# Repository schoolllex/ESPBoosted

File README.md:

# Custom ESP32-WROOM-32 All-in-One DevBoard

A custom, feature-rich ESP32-WROOM-32 development board featuring built-in environmental sensors, power management, and expansion interfaces. All project files, schematics, and manufacturing assets are included in the `.zip` archive within this repository.

## Features

* **Core & Programming:** ESP32-WROOM-32E module with onboard CH340K USB-to-UART bridge and automatic flash circuit.
* **Power Management:** AP2112K-3.3 LDO regulator, TP4056 LiPo battery charger, and power path management.
* **Sensors & Peripherals:**
* BME280 (Temperature, Humidity, Pressure)
* TSL25911FN (Digital Light Sensor)
* MPU-6050 (6-axis IMU / Accelerometer & Gyroscope)
* WS2812B RGB NeoPixel LED & Passive Piezo Buzzer
* MicroSD Card Slot (SPI mode)

* **Expansion:** MCP23017 16-bit I/O expander, ADS1115 16-bit ADC, and a Qwiic/STEMMA QT connector.

## Getting Started

1. Download and extract the project files from the `.zip` archive in this repository.
2. Open the project in **KiCad** to view schematics, layouts, and manufacturing files (Gerber/BOM/CPL).
3. Connect the board to your computer via a USB-C cable.
4. Flash your code using the Arduino IDE or your preferred development environment.
5. Enjoy your custom DevBoard!

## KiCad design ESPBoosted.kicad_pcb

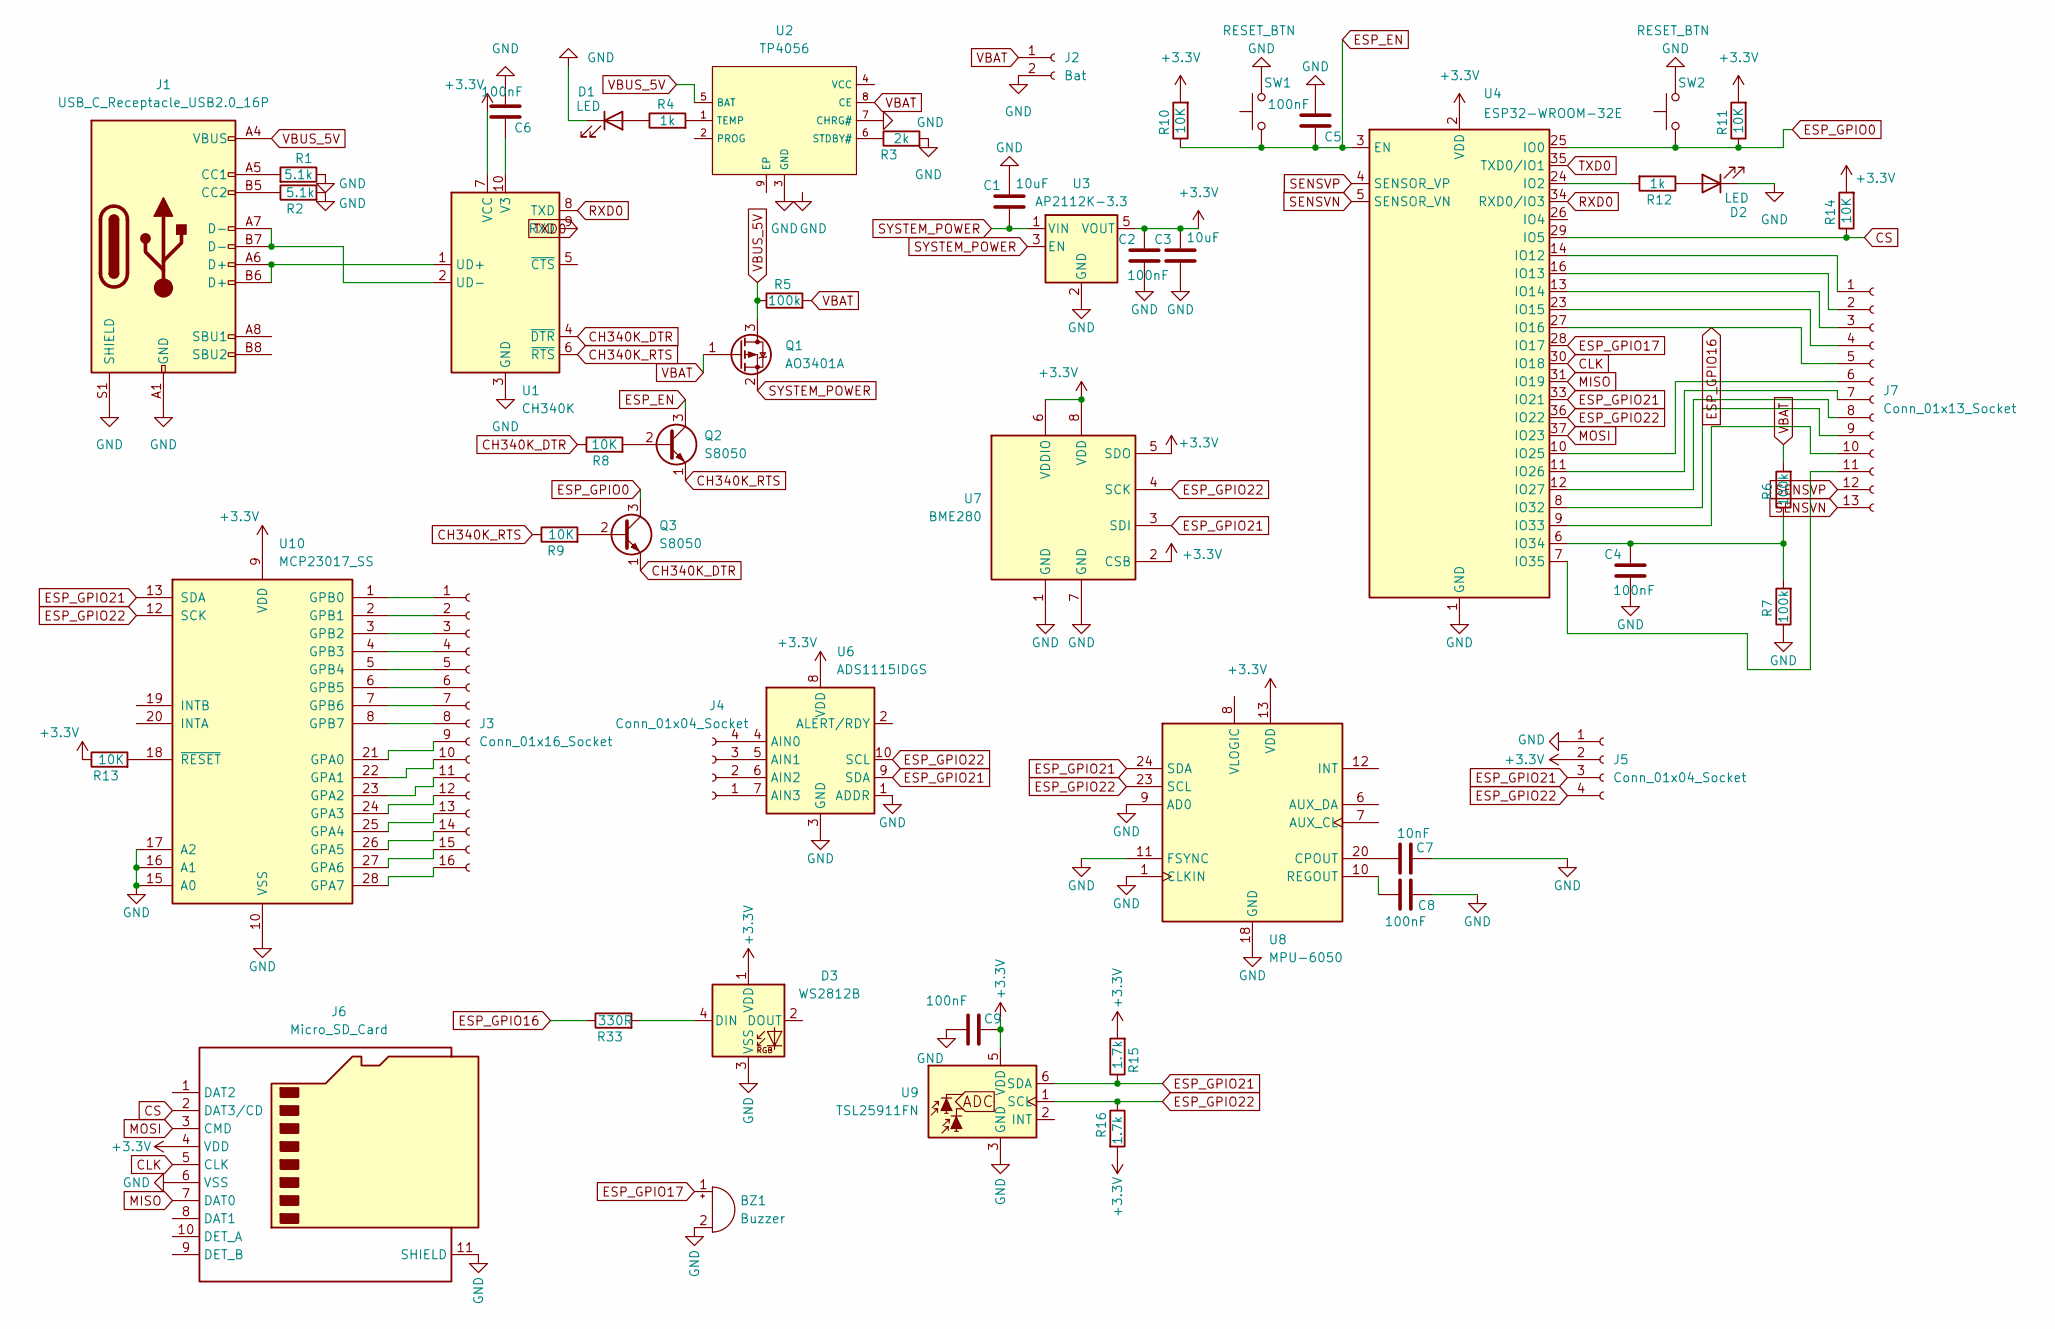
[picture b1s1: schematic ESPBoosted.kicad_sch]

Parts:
BZ1: Buzzer; Buzzer_CUI_CPT-9019S-SMT
C1, C3: 10uF; C_0805_2012Metric
C2, C4, C5, C6, C8, C9: 100nF; C_0805_2012Metric
C7: 10nF; C_0805_2012Metric
D1, D2: LED; LED_WS2812B_PLCC4_5.0x5.0mm_P3.2mm
D3: WS2812B; LED_WS2812B_PLCC4_5.0x5.0mm_P3.2mm
J1: USB_C_Receptacle_USB2.0_16P; USB_C_Receptacle_HRO_TYPE-C-31-M-12
J2: Bat; TerminalBlock_bornier-2_P5.08mm
J3: Conn_01x16_Socket; PinHeader_1x16_P1.00mm_Horizontal
J4, J5: Conn_01x04_Socket; PinHeader_1x04_P1.00mm_Horizontal
J6: Micro_SD_Card; microSD_HC_Hirose_DM3AT-SF-PEJM5
J7: Conn_01x13_Socket; PinHeader_1x13_P1.00mm_Horizontal
Q1: AO3401A; SOT-23
Q2, Q3: S8050; TO-92_Inline
R1, R2: 5.1k; R_0805_2012Metric
R3: 2k; R_0805_2012Metric
R4, R12: 1k; R_0805_2012Metric
R5, R6, R7: 100k; R_0805_2012Metric
R8, R9, R10, R11, R13, R14: 10K; R_0805_2012Metric
R15, R16: 1.7k; R_0805_2012Metric
R33: 330R; R_0805_2012Metric
SW1, SW2: RESET_BTN; SW_SPST_PTS645
U1: CH340K; SSOP-10-1EP_3.9x4.9mm_P1mm_EP2.1x3.3mm
U2: TP4056; HSOP-8-1EP_3.9x4.9mm_P1.27mm_EP2.3x2.3mm_ThermalVias; Part TP4056-42-ESOP8; LCSC C16581
U3: AP2112K-3.3; SOT-23-5
U4: ESP32-WROOM-32E; ESP32-WROOM-32
U6: ADS1115IDGS; MSOP-10_3x3mm_P0.5mm
U7: BME280; Bosch_LGA-8_2.5x2.5mm_P0.65mm_ClockwisePinNumbering
U8: MPU-6050; InvenSense_QFN-24_4x4mm_P0.5mm
U9: TSL25911FN; Broadcom_DFN-6_2x2mm_P0.65mm
U10: MCP23017_SS; SSOP-28_5.3x10.2mm_P0.65mm

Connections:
+3.3V: C2.1, C3.1, C9.2, D3.1 (VDD), J5.2, J6.4 (VDD), R10.2, R11.2, R13.1, R14.2, R15.2, R16.2, U1.7 (VCC), U3.5 (VOUT), U4.2 (VDD), U6.8 (VDD), U7.2 (CSB), U7.5 (SDO), U7.6 (VDDIO), U7.8 (VDD), U8.13 (VDD), U9.5 (VDD), U10.9 (VDD)
CH340K_DTR: Q3.1 (E), R8.1, U1.4 (~DTR)
CH340K_RTS: Q2.1 (E), R9.1, U1.6 (~RTS)
CLK: J6.5 (CLK), U4.30 (IO18)
CS: J6.2 (DAT3/CD), R14.1, U4.29 (IO5)
ESP_EN: C5.1, Q2.3 (C), R10.1, SW1.1, U4.3 (EN)
ESP_GPIO0: Q3.3 (C), R11.1, SW2.1, U4.25 (IO0)
ESP_GPIO16: J7.5, R33.1, U4.27 (IO16)
ESP_GPIO17: BZ1.1 (+), U4.28 (IO17)
ESP_GPIO21: J5.3, R15.1, U4.33 (IO21), U6.9 (SDA), U7.3 (SDI), U8.24 (SDA), U9.6 (SDA), U10.13 (SDA)
ESP_GPIO22: J5.4, R16.1, U4.36 (IO22), U6.10 (SCL), U7.4 (SCK), U8.23 (SCL), U9.1 (SCL), U10.12 (SCK)
GND: BZ1.2 (-), C1.1, C2.2, C3.2, C4.2, C5.2, C6.2, C7.2, C8.2, C9.1, D1.1 (K), D2.1 (K), D3.3 (VSS), J1.A1 (GND), J1.A12 (GND), J1.B1 (GND), J1.B12 (GND), J1.S1 (SHIELD), J2.2, J5.1, J6.6 (VSS), J6.11 (SHIELD), R1.1, R2.2, R3.2, R7.1, SW1.2, SW2.2, U1.3 (GND), U1.11 (GND), U2.3 (GND), U2.7 (CHRG#), U3.2 (GND), U4.1 (GND), U4.15 (GND), U4.38 (GND), U4.39 (GND), U6.1 (ADDR), U6.3 (GND), U7.1 (GND), U7.7 (GND), U8.1 (CLKIN), U8.9 (AD0), U8.11 (FSYNC), U8.18 (GND), U9.3 (GND), U10.10 (VSS), U10.15 (A0), U10.16 (A1), U10.17 (A2)
MISO: J6.7 (DAT0), U4.31 (IO19)
MOSI: J6.3 (CMD), U4.37 (IO23)
unnamed: D1.2 (A), R4.1
unnamed: D2.2 (A), R12.1
unnamed: D3.4 (DIN), R33.2
unnamed: J1.A5 (CC1), R1.2
unnamed: J1.B5 (CC2), R2.1
unnamed: J3.1, U10.1 (GPB0)
unnamed: J3.2, U10.2 (GPB1)
unnamed: J3.3, U10.3 (GPB2)
unnamed: J3.4, U10.4 (GPB3)
unnamed: J3.5, U10.5 (GPB4)
unnamed: J3.6, U10.6 (GPB5)
unnamed: J3.7, U10.7 (GPB6)
unnamed: J3.8, U10.8 (GPB7)
unnamed: J3.9, U10.21 (GPA0)
unnamed: J3.10, U10.22 (GPA1)
unnamed: J3.11, U10.23 (GPA2)
unnamed: J3.12, U10.24 (GPA3)
unnamed: J3.13, U10.25 (GPA4)
unnamed: J3.14, U10.26 (GPA5)
unnamed: J3.15, U10.27 (GPA6)
unnamed: J3.16, U10.28 (GPA7)
unnamed: J4.1, U6.7 (AIN3)
unnamed: J4.2, U6.6 (AIN2)
unnamed: J4.3, U6.5 (AIN1)
unnamed: J4.4, U6.4 (AIN0)
unnamed: J7.1, U4.14 (IO12)
unnamed: J7.2, U4.16 (IO13)
unnamed: J7.3, U4.13 (IO14)
unnamed: J7.4, U4.23 (IO15)
unnamed: J7.6, U4.10 (IO25)
unnamed: J7.7, U4.11 (IO26)
unnamed: J7.8, U4.12 (IO27)
unnamed: J7.9, U4.8 (IO32)
unnamed: J7.10, U4.9 (IO33)
unnamed: J7.11, U4.7 (IO35)
unnamed: Q2.2 (B), R8.2
unnamed: Q3.2 (B), R9.2
unnamed: J1.A6 (D+), J1.B6 (D+), U1.1 (UD+)
unnamed: J1.A7 (D-), J1.B7 (D-), U1.2 (UD-)
unnamed: C6.1, U1.10 (V3)
unnamed: R3.1, U2.6 (STDBY#)
unnamed: R4.2, U2.1 (TEMP)
unnamed: R12.2, U4.24 (IO2)
unnamed: C4.1, R6.1, R7.2, U4.6 (IO34)
unnamed: C7.1, U8.20 (CPOUT)
unnamed: C8.1, U8.10 (REGOUT)
unnamed: R13.2, U10.18 (~RESET)
RXD0: U1.8 (TXD), U4.34 (RXD0/IO3)
SENSVN: J7.13, U4.5 (SENSOR_VN)
SENSVP: J7.12, U4.4 (SENSOR_VP)
SYSTEM_POWER: C1.2, Q1.2 (S), U3.1 (VIN), U3.3 (EN)
TXD0: U1.9 (RXD), U4.35 (TXD0/IO1)
VBAT: J2.1, Q1.1 (G), R5.2, R6.2, U2.8 (CE)
VBUS_5V: J1.A4 (VBUS), J1.A9 (VBUS), J1.B4 (VBUS), J1.B9 (VBUS), Q1.3 (D), R5.1, U2.5 (BAT)

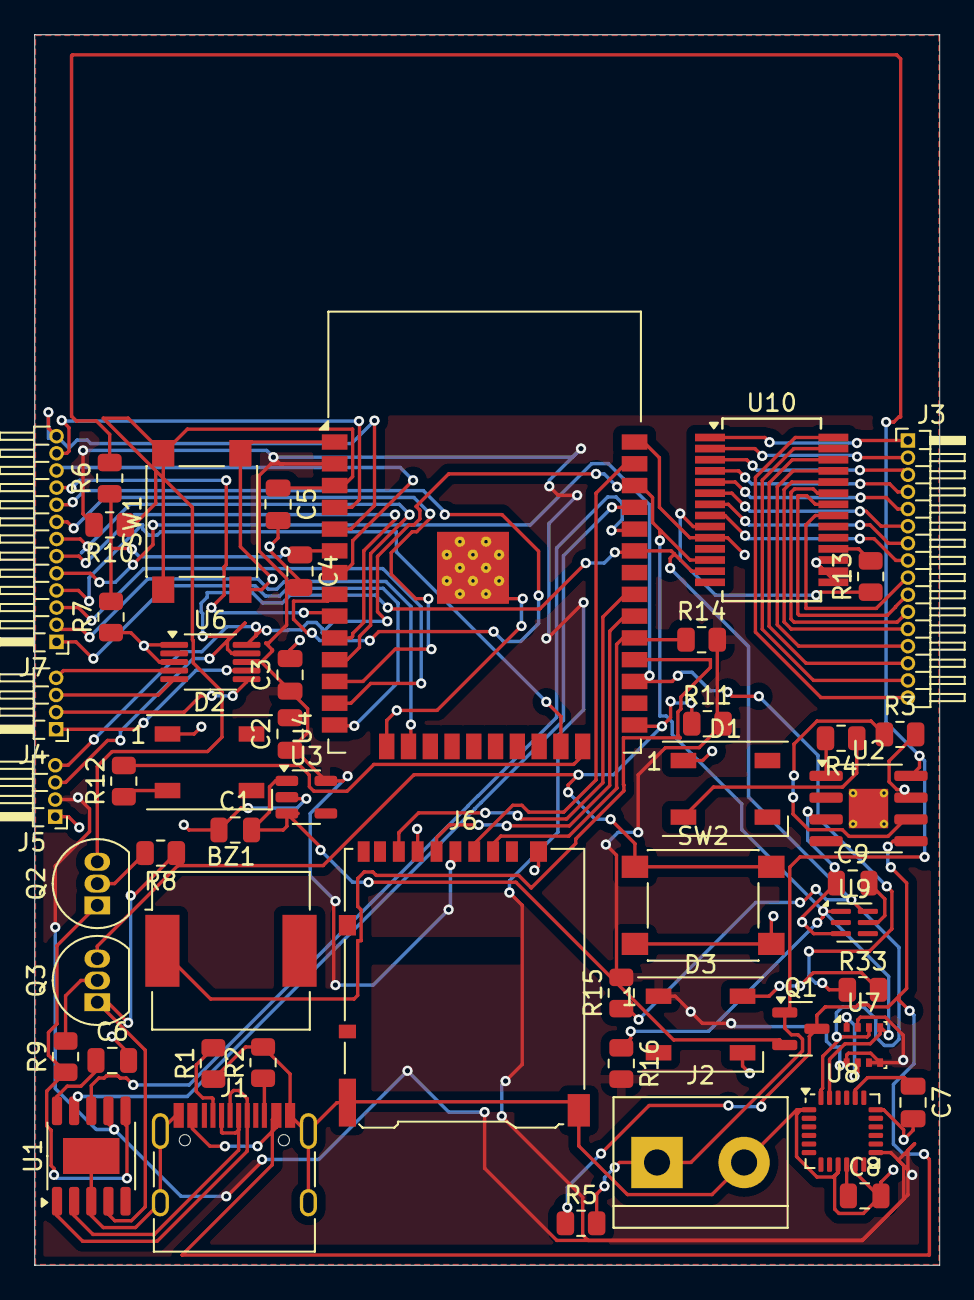
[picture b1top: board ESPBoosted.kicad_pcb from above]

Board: 2 copper layers, 52.8 x 71.8 mm, 51 parts (0 on the bottom side), 68 nets.
